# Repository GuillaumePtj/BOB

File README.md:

# BOB

This project is carried out by a for students group in second year at ENSEA.

### Principal objectives

This project main goal is to realize a 5-axis robot arm. This robot is a prototype concive to help people with disabilities. 

### Requirement

This project is realized in collaboration with a clinique, and some decision were taken.
The robot need :

  * to draw its power supply from the grid
  * to be able to pick up something from the floor where he stand
  * to be connected at the wheelchair of the patient in bluetooth
  * to be controled by the bluetooth and by a touch interface
  * to be fixed on a table 

Some decision where also taken for some technical reasons.
The robot :

  * contain a raspberry PI 4, and a STM32
  * present a total of 3 servomotors ans 3 steppers

---------------

# The realisation

### Mecanics

 The majority of the parts are modeled on SOLIDWORKS, and printed in 3D by the school. The mecanical parts (rollings, belt,...) are bought on RScomponents.  
Some other parts are given by the mechanical workshop.  
Files are available in the Meca branch.

-----
### Hardware

The hardware part is composed by 5 main devices :

 * The STM32
 * The Raspberry PI 4
 * The AC/DC converter
 * The power module
 * The driver module

All those devices are placed in the robot base and connected by cable to each other, and to other parts.  
The Raspberry is needed here because she offer wi-fi, bluetooth, serial connection, and good performances.  
STM32 is used because of his great ability to real time work, which is better for motor control.  
AC/DC converter take the 230V / 50Hz in input and comes out of 24V.  
The power module take the 24V, and divide it to provide 12V, 7.4V, 5V, and 3.3V.  
The driver module contain 4 driver for stepper.
All the PCB are designed on kiCad

-----
### Software

The Python code has been written on VSCode, and C code has been written on STM32CubeIDE.
All the codes are available in Code branch.

### Raspberry code

The Raspberry has already been configurate by activating SSH protocole and Wi-Fi.

**code actually runing into the robot**  
The raspberry and the STM communicate in UART. The raspberry sends the positioning data destined for a single motor to the STM with one single data frame of 7 bytes.
In order we have:  
Start of frame, engine number, engine angle, direction of rotation, rotation Speed, end of frame.
 
**Drafted but needs to be implemented later**  
We take the base of the first code except that this time we seek to direct the motors with the coordinates according to the X, Y, Z positions of our reference.
The frame sent is the following this time made of :  
Start of frame, Position along X and around X, Position along Y and around Y, Position along Z and around Z, End of frame.

More information in the "matrix" section

### STM32 code

Step to receive and use the data frame by UART :
- UART port binary speed: 9600  in interrupt mode 
- In CallBack function : Set a flag then receive the data frame into an integer array
- In the main function : We split the data written in the array
- Send the data to the motors

The datas received are : motor number, wanted angle, direction and speed.
The wrist and the gripper are controlled with servo motors. Shoulder and elbow are controlled by stepper motors.
When the robot is initialized, the servomotors move to their "central" position and their LEDs are green. After a short time they turn purple and the robot is ready to receive instructions.

**Speed control :**

The stepper motors can be controlled with 3 different speeds which are managed by three differently set timers. For the servos we gave a value between 0 and 1023. The higher this number, the faster the motor will go. We have preset 3 different speeds for them too.

**Direction control :** 

For both types of motors, the direction is a bit of 0 or 1. The only difference between the two types of motors is that the servos cannot be rotated indefinitely. For each direction it has an angle of action of 150°, so 300° in total.

**Angle control :**

### Direction of the motors in the state of the pins

Motor 1 (Clamp) : 
 * 0->close
 * 1->open
 
Motor 2 (Wirst_Z) : 
 * 0->left
 * 1->right

Motor 3 (Wirst_X) : 
 * 0 -> down
 * 1 -> up

Motor 4 (Elbow) : 
 * 0 -> up
 * 1 -> down

-----
### Matrix system

Now that we are controlling the motors 1 by 1 by giving the angle command to each of the motors, it is time to control the motor in position. To put this into practice we have to go through a matrix system.  
The matrix system will allow us to find the angles that each motor must adopt for the robot to reach a desired position.

Ex :  
the Raspberry sends the following instructions to the STM:  
 * X Position
 * Y Position
 * Z Position
 * X orientation
 * Y orientation
 * Z orientation
 
 and with these instructions the robot should be able to get into the desired position.
 
It is necessary to establish the "direct geometric model" (this makes it possible to obtain the final position thanks to the angles of the given motors) and invert this model. In our case, we therefore use the "inverse geometric model" which makes it the opposite of the previous model: from a given position, the model calculates the angles for each motor and that is what we want.

What has already been done:

- The inverse geometry model has been established for the first 3 axes, the equations and the code have been written for the first 3 axes. All that's missing is to take into account the reduction ratios of each engine and add the factors in the code and then test the whole thing.

What remains to be done :

- Establish the inverse geometric model for the remaining 2 axes.

Good to know :

The inverse geometric model of the robot is done in two stages (position part and orientation part). The position part of the robot is done (part which manages the first 3 axes) and the orientation part (orientation of the gripper) which is managed by the remaining axes is to be done. For the resolution of the inverse geometry model of the last axes, it is necessary:

 1) establish the direct geometric model using the Denavit-Hartenberg method
 2) Inverse the model by using PAUL's method
 3) Once the equations of the remaining angles have been found, implement it in the STM
 
----------
### To go further

Some parts needs to be adapted, like the shoulder, the cable management, or the placement of the cards into the basement. 
The driver PCB doesn't work correctly, some debugging is needed.
The robot could be better with a last rotary axis, beetween the elbow and the wrist.  
The contrôle part as begun. But she is not implemented due to a bluetooth probleme and the fact that there is one articulation less.
The code in python need to work with interrupt so that we can use the Raspberry for interfacing while she send data frame.

----------
here is the datasheet of the [driver](https://www.trinamic.com/fileadmin/assets/Products/ICs_Documents/TMC2225_Datasheet_Rev1.11.pdf) for the steppers.  
here is the datasheet of the [servomotors](https://emanual.robotis.com/docs/en/dxl/x/xl320/).  
here is the documentation for the [STM32](https://www.st.com/resource/en/datasheet/stm32l412kb.pdf).

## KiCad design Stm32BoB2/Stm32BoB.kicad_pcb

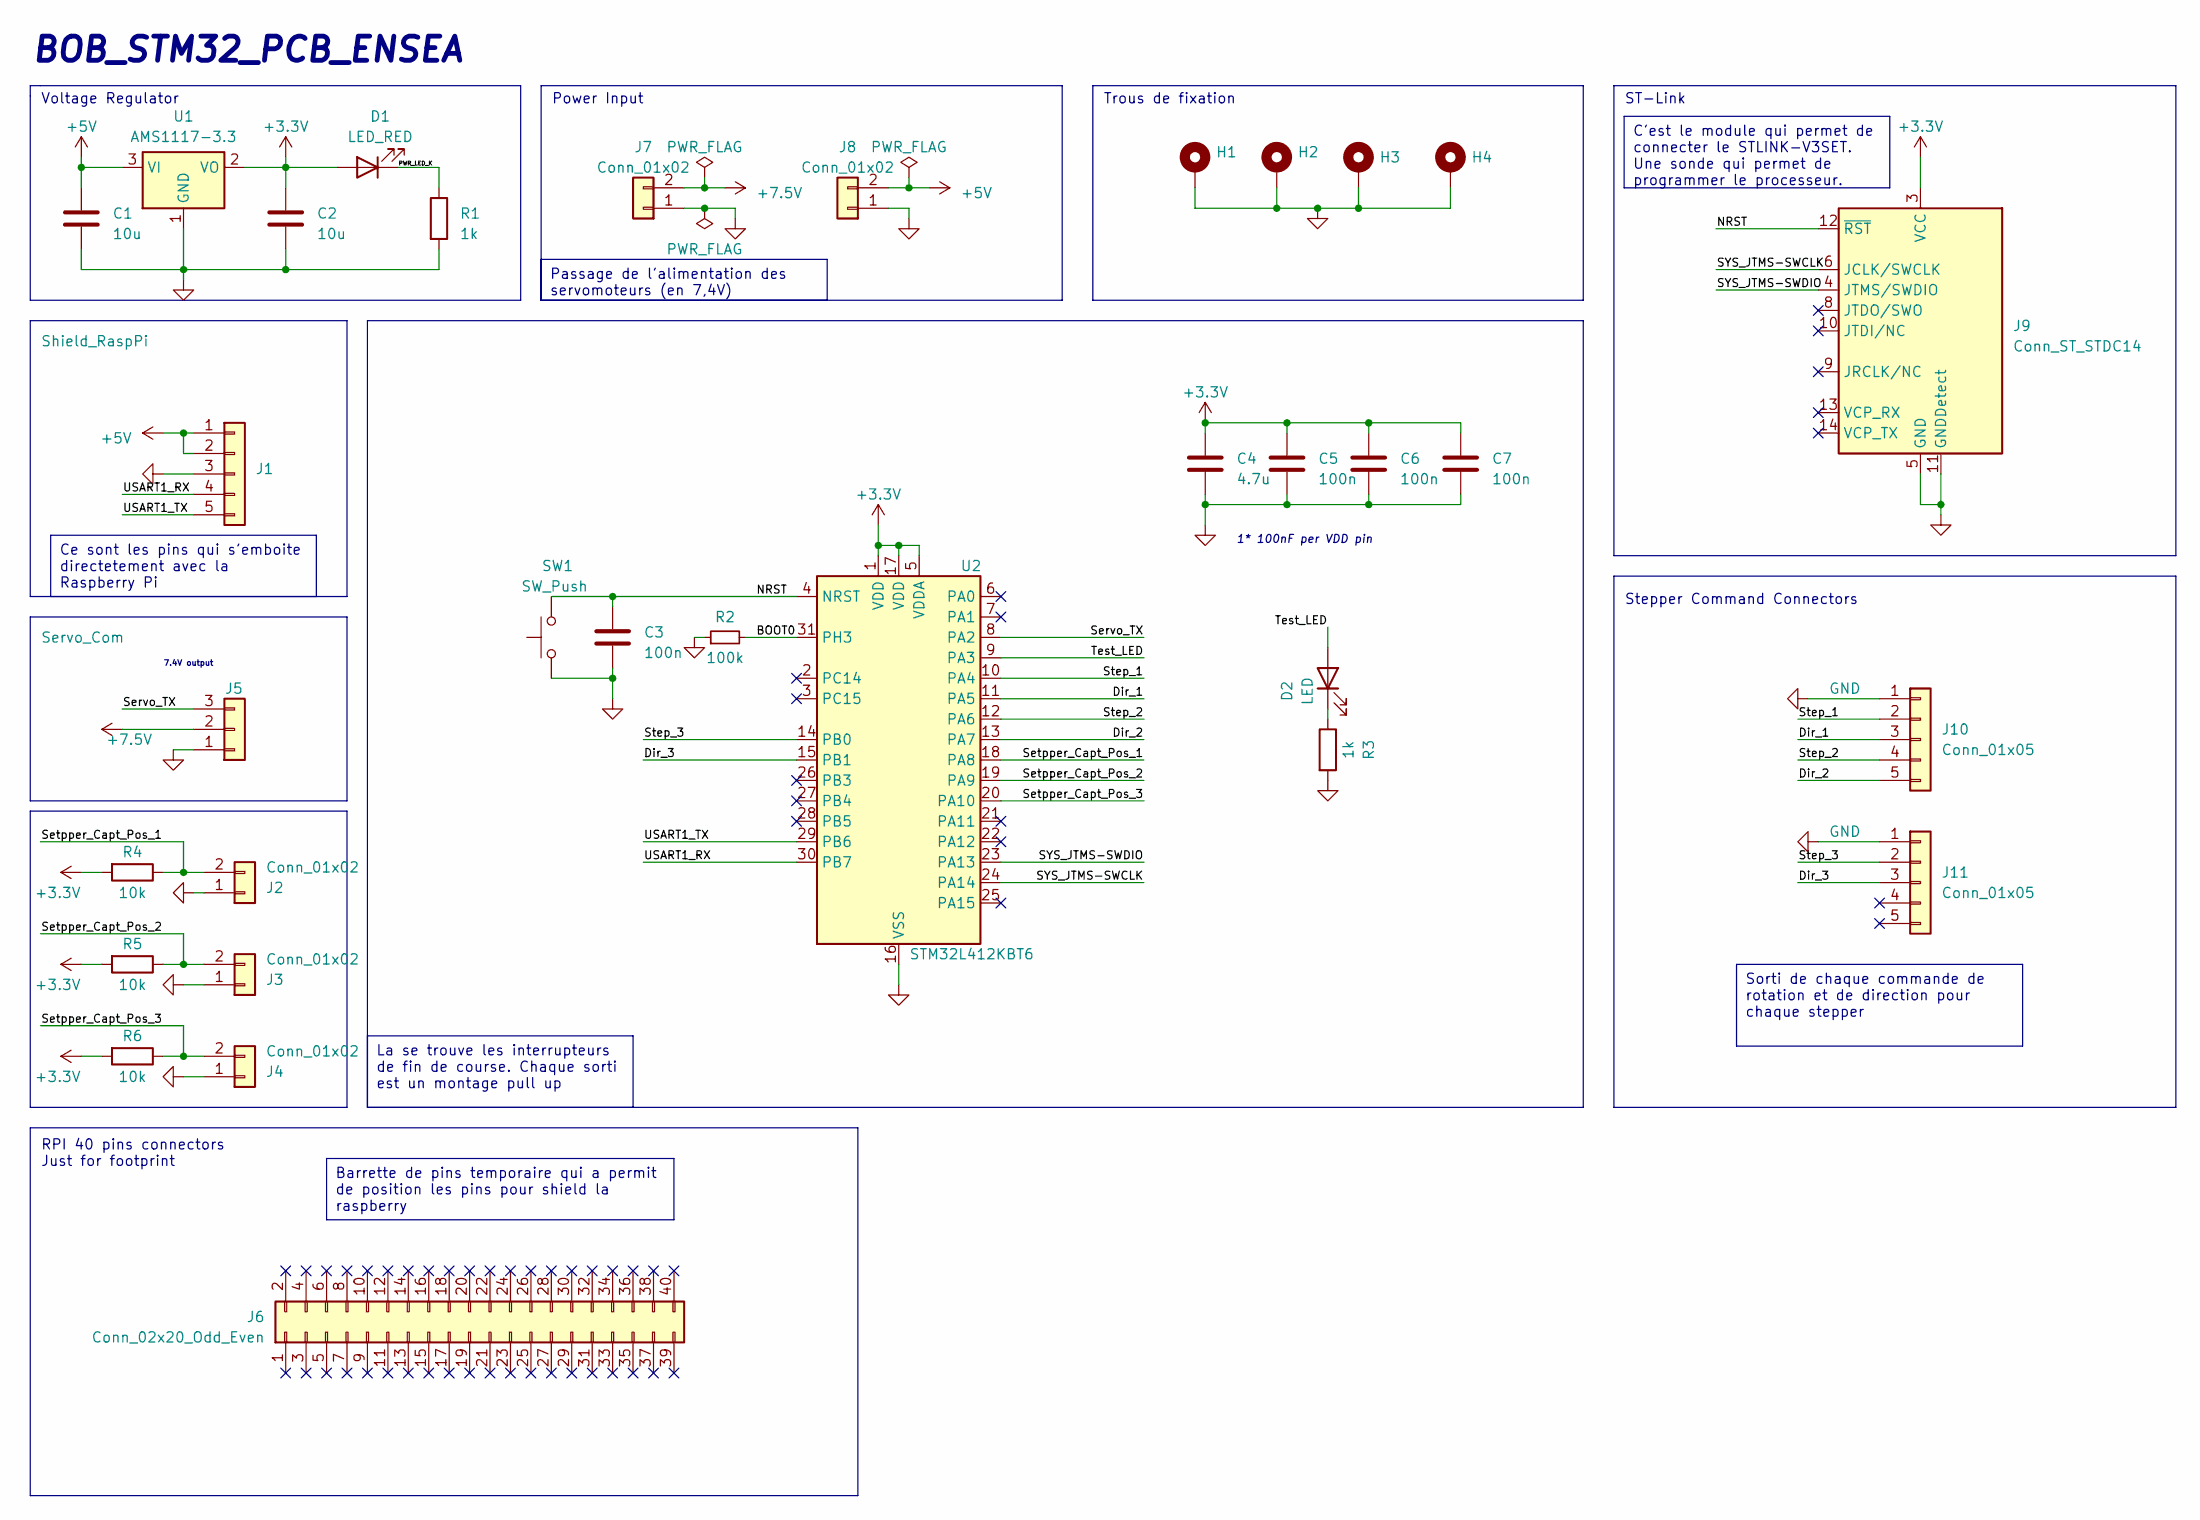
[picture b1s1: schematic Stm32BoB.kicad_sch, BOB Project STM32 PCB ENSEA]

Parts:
C1, C2: 10u; C_0603_1608Metric_Pad1.08x0.95mm_HandSolder
C3, C5, C6, C7: 100n; C_0603_1608Metric_Pad1.08x0.95mm_HandSolder
C4: 4.7u; C_0603_1608Metric_Pad1.08x0.95mm_HandSolder
D1: LED_RED; LED_0603_1608Metric_Pad1.05x0.95mm_HandSolder
D2: LED; LED_0603_1608Metric_Pad1.05x0.95mm_HandSolder
H1, H2, H3, H4: MountingHole_Pad; MountingHole_2.7mm_Pad_Via
J1: Shield_RaspPi; PinSocket_1x05_P2.54mm_Vertical
J2, J3, J4, J7, J8: Conn_01x02; JST_XH_B2B-XH-A_1x02_P2.50mm_Vertical
J5: Servo_Com; JST_XH_B3B-XH-A_1x03_P2.50mm_Vertical
J6: Conn_02x20_Odd_Even; PinHeader_2x20_P2.54mm_Vertical
J9: Conn_ST_STDC14; PinHeader_2x07_P1.27mm_Vertical_SMD
J10, J11: Conn_01x05; JST_XH_B5B-XH-A_1x05_P2.50mm_Vertical
R1, R3: 1k; R_0603_1608Metric_Pad0.98x0.95mm_HandSolder
R2: 100k; R_0603_1608Metric_Pad0.98x0.95mm_HandSolder
R4, R5, R6: 10k; R_0603_1608Metric_Pad0.98x0.95mm_HandSolder
SW1: SW_Push; SW_SPST_B3U-1000P
U1: AMS1117-3.3; SOT-223-3_TabPin2
U2: STM32L412KBT6; LQFP-32_7x7mm_P0.8mm

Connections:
+3.3V: C2.1, C4.1, C5.1, C6.1, C7.1, D1.2 (A), J9.3 (VCC), R4.2, R5.2, R6.2, U1.2 (VO), U2.1 (VDD), U2.5 (VDDA), U2.17 (VDD)
+5V: C1.1, J1.1, J1.2, J8.2, U1.3 (VI)
+7.5V: J5.2, J7.2
/BOOT0: R2.2, U2.31 (PH3)
/Dir_1: J10.3, U2.11 (PA5)
/Dir_2: J10.5, U2.13 (PA7)
/Dir_3: J11.3, U2.15 (PB1)
/NRST: C3.2, J9.12 (~RST), SW1.2, U2.4 (NRST)
/PWR_LED_K: D1.1 (K), R1.1
/SYS_JTMS-SWCLK: J9.6 (JCLK/SWCLK), U2.24 (PA14)
/SYS_JTMS-SWDIO: J9.4 (JTMS/SWDIO), U2.23 (PA13)
/Servo_TX: J5.3, U2.8 (PA2)
/Setpper_Capt_Pos_1: J2.2, R4.1, U2.18 (PA8)
/Setpper_Capt_Pos_2: J3.2, R5.1, U2.19 (PA9)
/Setpper_Capt_Pos_3: J4.2, R6.1, U2.20 (PA10)
/Step_1: J10.2, U2.10 (PA4)
/Step_2: J10.4, U2.12 (PA6)
/Step_3: J11.2, U2.14 (PB0)
/Test_LED: D2.2 (A), U2.9 (PA3)
/USART1_RX: J1.4, U2.30 (PB7)
/USART1_TX: J1.5, U2.29 (PB6)
GND: C1.2, C2.2, C3.1, C4.2, C5.2, C6.2, C7.2, H1.1, H2.1, H3.1, H4.1, J1.3, J2.1, J3.1, J4.1, J5.1, J7.1, J8.1, J9.5 (GND), J9.7 (GND), J9.11 (GNDDetect), J10.1, J11.1, R1.2, R2.1, R3.2, SW1.1, U1.1 (GND), U2.16 (VSS), U2.32 (VSS)
unnamed: D2.1 (K), R3.1

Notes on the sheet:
Ce sont les pins qui s'emboite directetement avec la Raspberry Pi
Passage de l'alimentation des servomoteurs (en 7,4V)
La se trouve les interrupteurs de fin de course. Chaque sorti est un montage pull up
Sorti de chaque commande de rotation et de direction pour chaque stepper
Barrette de pins temporaire qui a permit de position les pins pour shield la raspberry
C'est le module qui permet de connecter le STLINK-V3SET. Une sonde qui permet de programmer le processeur.
7.4V output
BOB_STM32_PCB_ENSEA
ST-Link
Stepper Command Connectors
Power Input
Trous de fixation
1* 100nF per VDD pin
RPI 40 pins connectors Just for footprint
Voltage Regulator

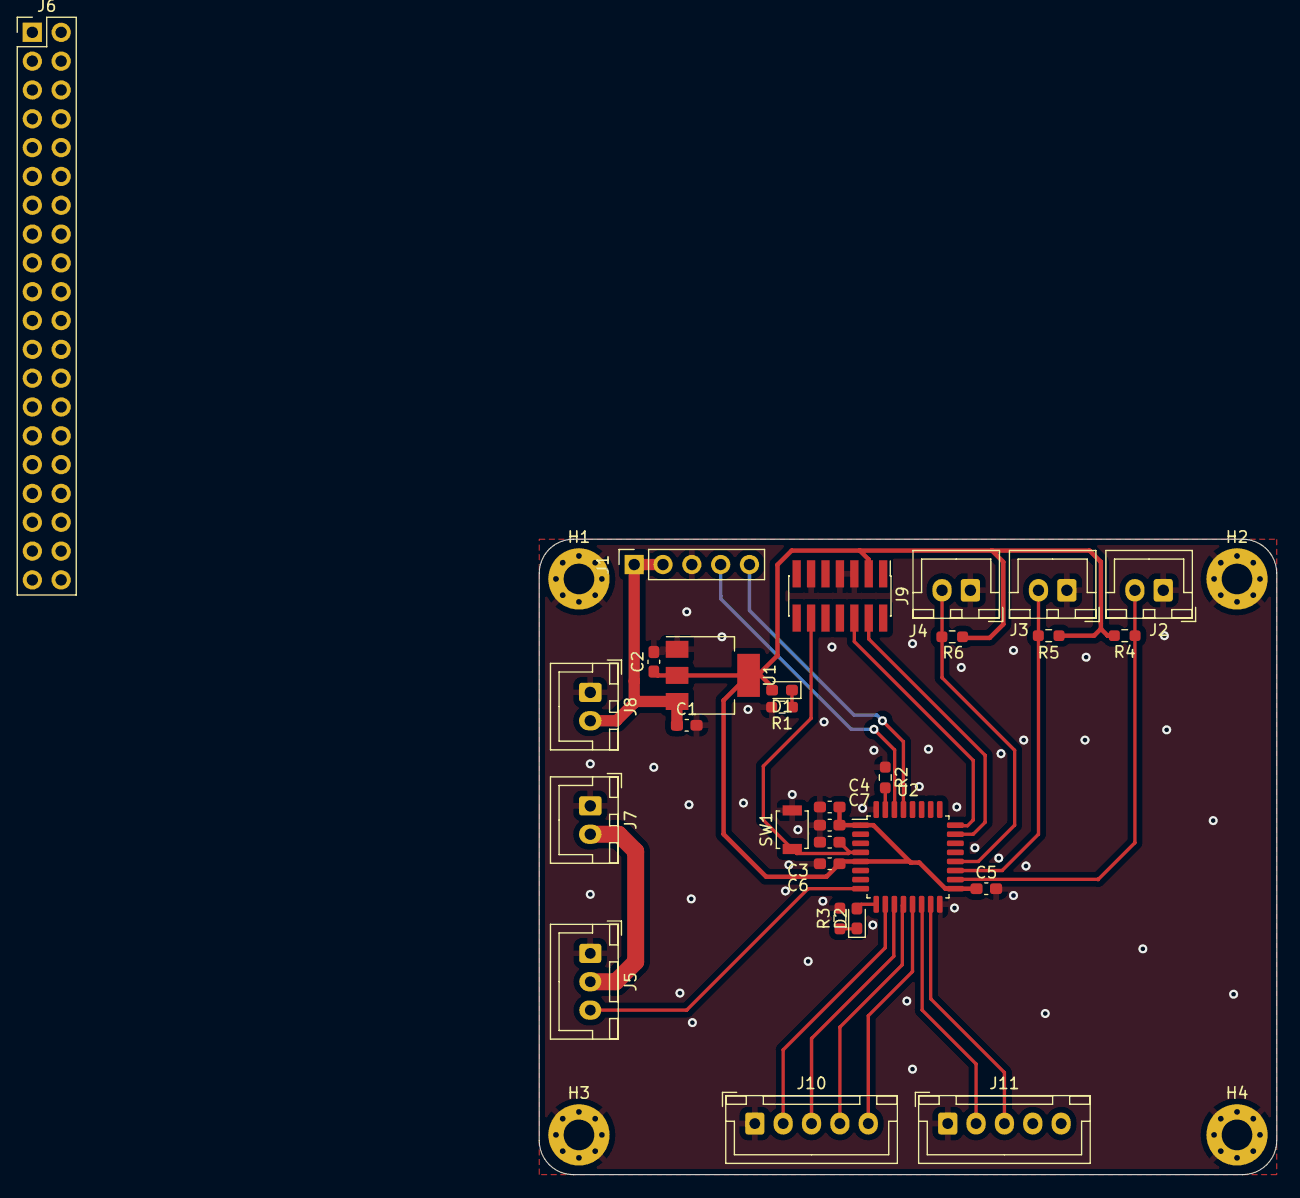
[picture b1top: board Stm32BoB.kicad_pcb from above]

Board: 2 copper layers, 65.0 x 56.0 mm, 33 parts (0 on the bottom side), 23 nets.

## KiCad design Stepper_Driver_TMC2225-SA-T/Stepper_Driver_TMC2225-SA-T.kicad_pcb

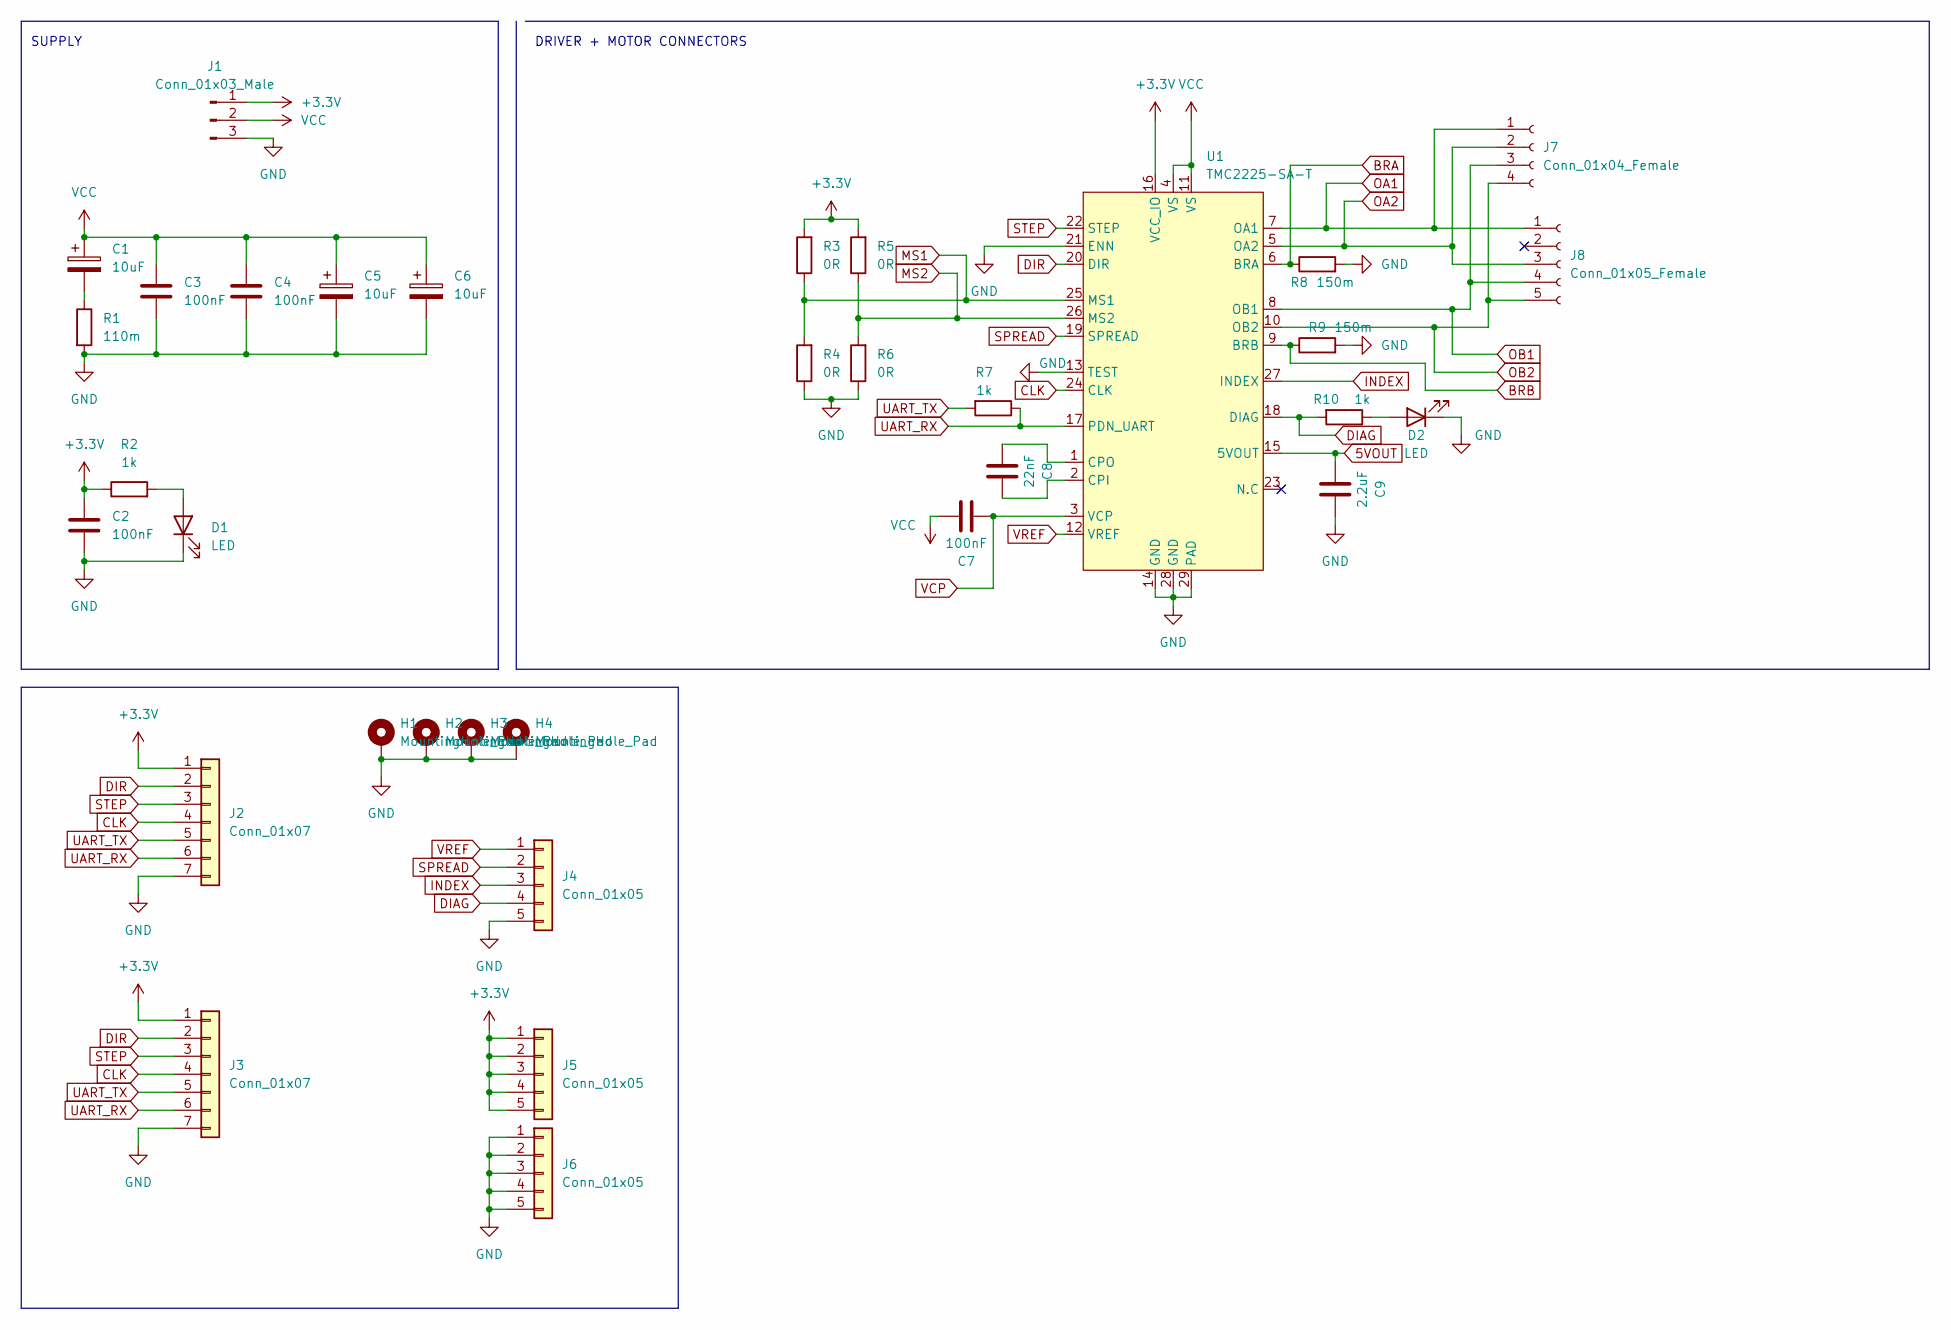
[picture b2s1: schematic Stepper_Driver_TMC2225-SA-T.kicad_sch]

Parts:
C1, C5, C6: 10uF; CP_Elec_4x5.7
C2, C3, C4, C7: 100nF; C_0603_1608Metric_Pad1.08x0.95mm_HandSolder
C8: 22nF; C_0603_1608Metric_Pad1.08x0.95mm_HandSolder
C9: 2.2uF; C_0805_2012Metric_Pad1.18x1.45mm_HandSolder
D1, D2: LED; LED_0603_1608Metric_Pad1.05x0.95mm_HandSolder
H1, H2, H3, H4: MountingHole_Pad; MountingHole_3.2mm_M3_Pad_Via
J1: Conn_01x03_Male; JST_XH_B3B-XH-A_1x03_P2.50mm_Vertical
J2: Conn_01x07; JST_XH_B7B-XH-A_1x07_P2.50mm_Vertical
J3: Conn_01x07; PinHeader_1x07_P2.54mm_Vertical
J4, J5, J6: Conn_01x05; PinHeader_1x05_P2.54mm_Vertical
J7: Conn_01x04_Female; JST_XH_B4B-XH-A_1x04_P2.50mm_Vertical
J8: Conn_01x05_Female; JST_XH_B5B-XH-A_1x05_P2.50mm_Vertical
R1: 110m; R_0603_1608Metric_Pad0.98x0.95mm_HandSolder
R2, R7, R10: 1k; R_0603_1608Metric_Pad0.98x0.95mm_HandSolder
R3, R4, R5, R6: 0R; R_0603_1608Metric_Pad0.98x0.95mm_HandSolder
R8, R9: 150m; R_1206_3216Metric_Pad1.30x1.75mm_HandSolder
U1: TMC2225-SA-T; HTSSOP-28-1EP_4.4x9.7mm_P0.65mm_EP2.85x5.4mm_ThermalVias

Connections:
5VOUT: C9.2, U1.15 (5VOUT)
+3.3V: C2.1, J1.1, J2.1, J3.1, J5.1, J5.2, J5.3, J5.4, J5.5, R2.1, R3.2, R5.2, U1.16 (VCC_IO)
BRA: R8.1, U1.6 (BRA)
BRB: R9.1, U1.9 (BRB)
CLK: J2.4, J3.4, U1.24 (CLK)
DIAG: J4.4, R10.2, U1.18 (DIAG)
DIR: J2.2, J3.2, U1.20 (DIR)
GND: C2.2, C3.2, C4.2, C5.2, C6.2, C9.1, D1.1 (K), D2.1 (K), H1.1, H2.1, H3.1, H4.1, J1.3, J2.7, J3.7, J4.5, J6.1, J6.2, J6.3, J6.4, J6.5, R1.2, R4.1, R6.1, R8.2, R9.2, U1.13 (TEST), U1.14 (GND), U1.21 (ENN), U1.28 (GND), U1.29 (PAD)
INDEX: J4.3, U1.27 (INDEX)
MS1: R3.1, R4.2, U1.25 (MS1)
MS2: R5.1, R6.2, U1.26 (MS2)
unnamed: C1.2, R1.1
unnamed: C8.1, U1.2 (CPI)
unnamed: C8.2, U1.1 (CPO)
unnamed: D1.2 (A), R2.2
unnamed: D2.2 (A), R10.1
OA1: J7.1, J8.1, U1.7 (OA1)
OA2: J7.2, J8.3, U1.5 (OA2)
OB1: J7.3, J8.4, U1.8 (OB1)
OB2: J7.4, J8.5, U1.10 (OB2)
SPREAD: J4.2, U1.19 (SPREAD)
STEP: J2.3, J3.3, U1.22 (STEP)
UART_RX: J2.6, J3.6, R7.1, U1.17 (PDN_UART)
UART_TX: J2.5, J3.5, R7.2
VCC: C1.1, C3.1, C4.1, C5.1, C6.1, C7.1, J1.2, U1.4 (VS), U1.11 (VS)
VCP: C7.2, U1.3 (VCP)
VREF: J4.1, U1.12 (VREF)

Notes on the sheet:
SUPPLY
DRIVER + MOTOR CONNECTORS

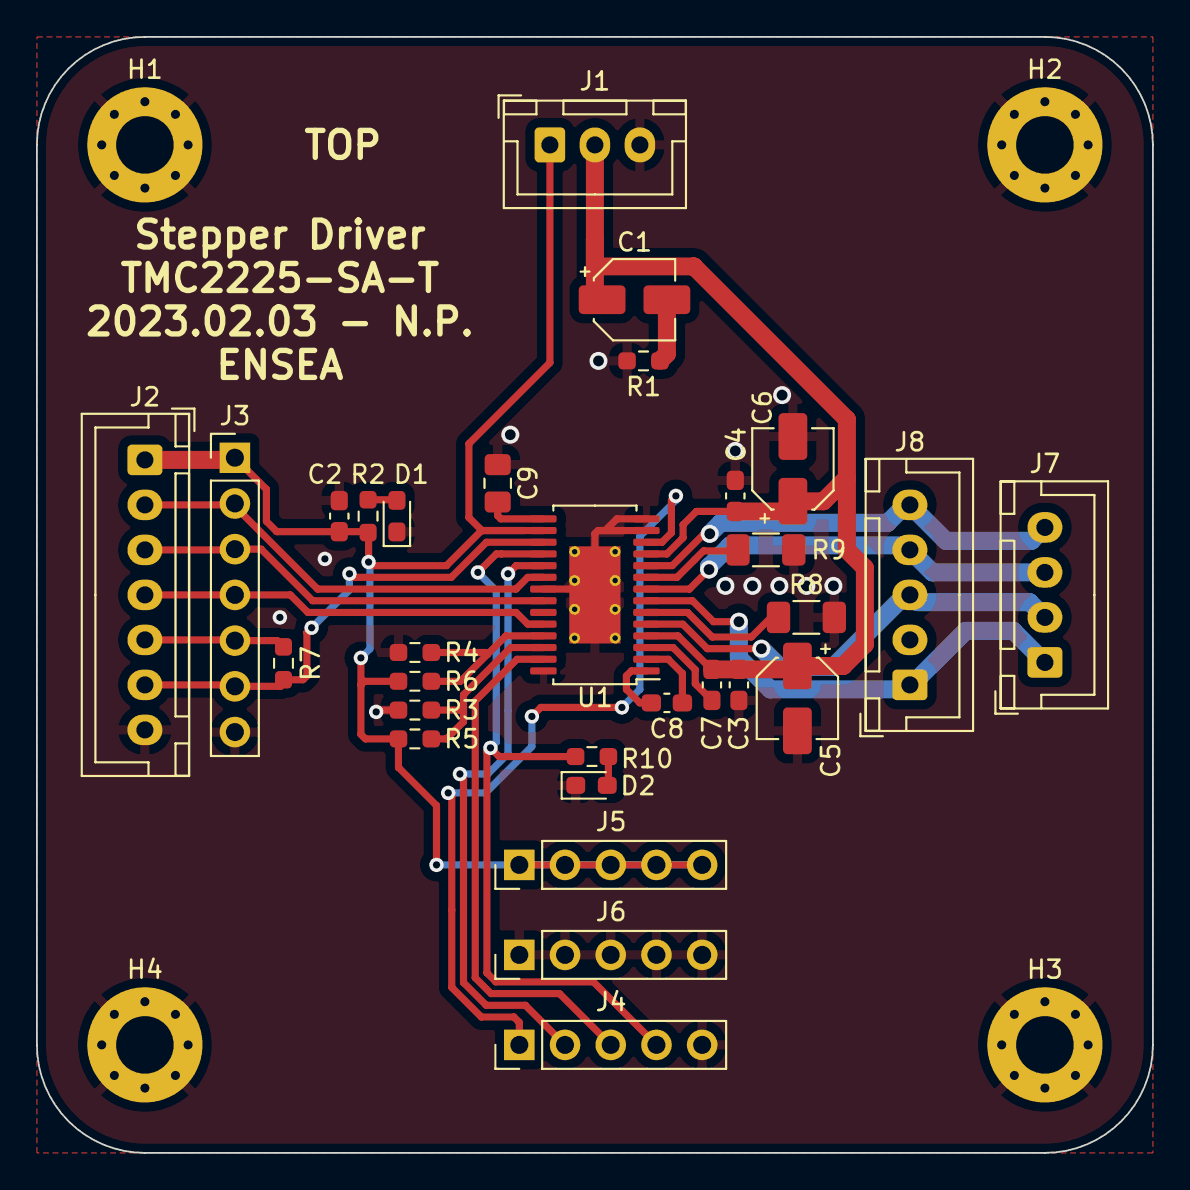
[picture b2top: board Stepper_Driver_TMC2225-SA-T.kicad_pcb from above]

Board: 2 copper layers, 62.0 x 62.0 mm, 34 parts (0 on the bottom side), 27 nets.

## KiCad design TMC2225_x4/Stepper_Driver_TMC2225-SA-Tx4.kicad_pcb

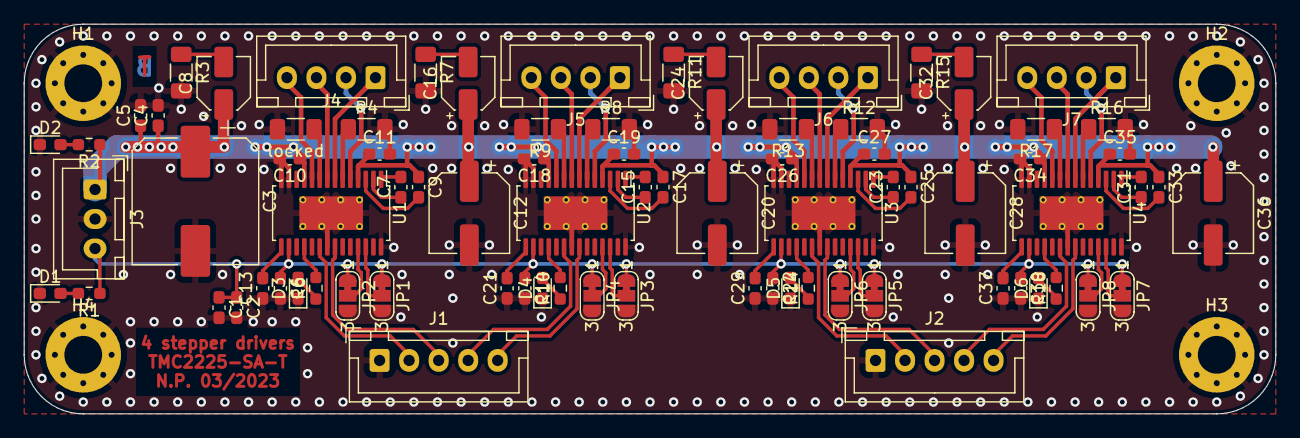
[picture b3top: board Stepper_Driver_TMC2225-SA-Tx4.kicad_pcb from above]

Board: 2 copper layers, 106.0 x 33.0 mm, 84 parts (0 on the bottom side), 73 nets.

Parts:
C1, C4: 1uF; C_0603_1608Metric_Pad1.08x0.95mm_HandSolder
C2, C5, C6, C9, C10, C11, C14, C17, C18, C19, C22, C25, C26, C27, C30, C33, C34, C35: 100nF; C_0603_1608Metric_Pad1.08x0.95mm_HandSolder
C3: 100uF; CP_Elec_10x10.5
C7, C15, C23, C31: 22nF; C_0603_1608Metric_Pad1.08x0.95mm_HandSolder
C8, C16, C24, C32: 10uF; CP_Elec_4x5.7
C12, C20, C28, C36: 100uF; CP_Elec_6.3x7.7
C13, C21, C29, C37: 2.2uF; C_0603_1608Metric_Pad1.08x0.95mm_HandSolder
D1, D2, D3, D4, D5, D6: LED; LED_0603_1608Metric_Pad1.05x0.95mm_HandSolder
H1, H2, H3, H4: MountingHole_Pad; MountingHole_3.2mm_M3_Pad_Via
J1, J2: Conn_01x05; JST_XH_B5B-XH-A_1x05_P2.50mm_Vertical
J3: Conn_01x03_Male; JST_XH_B3B-XH-A_1x03_P2.50mm_Vertical
J4, J5, J6, J7: Conn_01x04_Female; JST_XH_B4B-XH-A_1x04_P2.50mm_Vertical
JP1, JP2, JP3, JP4, JP5, JP6, JP7, JP8: SolderJumper_3_Bridged12; SolderJumper-3_P1.3mm_Bridged12_RoundedPad1.0x1.5mm_NumberL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
R1, R2, R6, R10, R14, R18: 1k; R_0603_1608Metric_Pad0.98x0.95mm_HandSolder
R3, R7, R11, R15: 110m; R_1206_3216Metric_Pad1.30x1.75mm_HandSolder
R4, R8, R9, R12, R13, R16, R17: 150m; R_1206_3216Metric_Pad1.30x1.75mm_HandSolder
U1, U2, U3, U4: TMC2225-SA-T; HTSSOP-28-1EP_4.4x9.7mm_P0.65mm_EP2.85x5.4mm_ThermalVias
locked: 150m; R_1206_3216Metric_Pad1.30x1.75mm_HandSolder

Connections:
+3.3V: C1.1, C2.1, C6.1, C14.1, C22.1, C30.1, J3.3, JP1.1 (A), JP2.1 (A), JP3.1 (A), JP4.1 (A), JP5.1 (A), JP6.1 (A), JP7.1 (A), JP8.1 (A), R1.1, U1.16 (VCC_IO), U2.16 (VCC_IO), U3.16 (VCC_IO), U4.16 (VCC_IO)
/TMC2225-1/BRA: R4.1, U1.6 (BRA)
/TMC2225-1/BRB: U1.9 (BRB), locked.1
/TMC2225-1/OA1: J4.1, U1.7 (OA1)
/TMC2225-1/OA2: J4.2, U1.5 (OA2)
/TMC2225-1/OB1: J4.3, U1.8 (OB1)
/TMC2225-1/OB2: J4.4, U1.10 (OB2)
/TMC2225-2/BRA: R8.1, U2.6 (BRA)
/TMC2225-2/BRB: R9.1, U2.9 (BRB)
/TMC2225-2/OA1: J5.1, U2.7 (OA1)
/TMC2225-2/OA2: J5.2, U2.5 (OA2)
/TMC2225-2/OB1: J5.3, U2.8 (OB1)
/TMC2225-2/OB2: J5.4, U2.10 (OB2)
/TMC2225-3/BRA: R12.1, U3.6 (BRA)
/TMC2225-3/BRB: R13.1, U3.9 (BRB)
/TMC2225-3/OA1: J6.1, U3.7 (OA1)
/TMC2225-3/OA2: J6.2, U3.5 (OA2)
/TMC2225-3/OB1: J6.3, U3.8 (OB1)
/TMC2225-3/OB2: J6.4, U3.10 (OB2)
/TMC2225-4/BRA: R16.1, U4.6 (BRA)
/TMC2225-4/BRB: R17.1, U4.9 (BRB)
/TMC2225-4/OA1: J7.1, U4.7 (OA1)
/TMC2225-4/OA2: J7.2, U4.5 (OA2)
/TMC2225-4/OB1: J7.3, U4.8 (OB1)
/TMC2225-4/OB2: J7.4, U4.10 (OB2)
DIR_1: J1.3, U1.22 (STEP)
DIR_2: J1.5, U2.22 (STEP)
DIR_3: J2.3, U3.22 (STEP)
DIR_4: J2.5, U4.22 (STEP)
GND: C1.2, C2.2, C3.2, C4.2, C5.2, C6.2, C10.2, C11.2, C12.2, C13.1, C14.2, C18.2, C19.2, C20.2, C21.1, C22.2, C26.2, C27.2, C28.2, C29.1, C30.2, C34.2, C35.2, C36.2, C37.1, D1.1 (K), D2.1 (K), D3.1 (K), D4.1 (K), D5.1 (K), D6.1 (K), H1.1, H2.1, H3.1, H4.1, J1.1, J2.1, J3.2, JP1.3 (B), JP2.3 (B), JP3.3 (B), JP4.3 (B), JP5.3 (B), JP6.3 (B), JP7.3 (B), JP8.3 (B), R3.2, R4.2, R7.2, R8.2, R9.2, R11.2, R12.2, R13.2, R15.2, R16.2, R17.2, U1.13 (TEST), U1.14 (GND), U1.21 (ENN), U1.28 (GND), U1.29 (PAD), U2.13 (TEST), U2.14 (GND), U2.21 (ENN), U2.28 (GND), U2.29 (PAD), U3.13 (TEST), U3.14 (GND), U3.21 (ENN), U3.28 (GND), U3.29 (PAD), U4.13 (TEST), U4.14 (GND), U4.21 (ENN), U4.28 (GND), U4.29 (PAD), locked.2
unnamed: C7.1, U1.2 (CPI)
unnamed: C7.2, U1.1 (CPO)
unnamed: C8.2, R3.1
unnamed: C9.2, U1.3 (VCP)
unnamed: C13.2, U1.15 (5VOUT)
unnamed: C15.1, U2.2 (CPI)
unnamed: C15.2, U2.1 (CPO)
unnamed: C16.2, R7.1
unnamed: C17.2, U2.3 (VCP)
unnamed: C21.2, U2.15 (5VOUT)
unnamed: C23.1, U3.2 (CPI)
unnamed: C23.2, U3.1 (CPO)
unnamed: C24.2, R11.1
unnamed: C25.2, U3.3 (VCP)
unnamed: C29.2, U3.15 (5VOUT)
unnamed: C31.1, U4.2 (CPI)
unnamed: C31.2, U4.1 (CPO)
unnamed: C32.2, R15.1
unnamed: C33.2, U4.3 (VCP)
unnamed: C37.2, U4.15 (5VOUT)
unnamed: D1.2 (A), R1.2
unnamed: D2.2 (A), R2.2
unnamed: D3.2 (A), R6.1
unnamed: D4.2 (A), R10.1
unnamed: D5.2 (A), R14.1
unnamed: D6.2 (A), R18.1
unnamed: JP1.2 (C), U1.26 (MS2)
unnamed: JP2.2 (C), U1.25 (MS1)
unnamed: JP3.2 (C), U2.26 (MS2)
unnamed: JP4.2 (C), U2.25 (MS1)
unnamed: JP5.2 (C), U3.26 (MS2)
unnamed: JP6.2 (C), U3.25 (MS1)
unnamed: JP7.2 (C), U4.26 (MS2)
unnamed: JP8.2 (C), U4.25 (MS1)
unnamed: R6.2, U1.18 (DIAG)
unnamed: R10.2, U2.18 (DIAG)
unnamed: R14.2, U3.18 (DIAG)
unnamed: R18.2, U4.18 (DIAG)
STEP_1: J1.2, U1.20 (DIR)
STEP_2: J1.4, U2.20 (DIR)
STEP_3: J2.2, U3.20 (DIR)
STEP_4: J2.4, U4.20 (DIR)
VCC: C3.1, C4.1, C5.1, C8.1, C9.1, C10.1, C11.1, C12.1, C16.1, C17.1, C18.1, C19.1, C20.1, C24.1, C25.1, C26.1, C27.1, C28.1, C32.1, C33.1, C34.1, C35.1, C36.1, J3.1, R2.1, U1.4 (VS), U1.11 (VS), U2.4 (VS), U2.11 (VS), U3.4 (VS), U3.11 (VS), U4.4 (VS), U4.11 (VS)
